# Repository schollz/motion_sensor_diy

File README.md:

motion_sensor_diy
=================

Electronic schematics for RF motion sensor that uses Arduino as receiver hub

Instructions
=================

The eagle schematics show the wiring for the Motion Sensor and the Receiver. Each is very simple, here is the run down:

<h1>Motion sensor + RF transmitter</h1>

<strong>Components</strong>
<ul>
<li><a href="https://www.google.com/url?sa=t&rct=j&q=&esrc=s&source=web&cd=6&cad=rja&uact=8&ved=0CDkQFjAF&url=http%3A%2F%2Fwww.mpja.com%2Fdownload%2F31227sc.pdf&ei=8FgzU868GsHLsQSTnYKIDg&usg=AFQjCNELdcZfKHaZhM4NlzFmhzu2_fOHwg&sig2=eFrgkllWo_47kU5vjeJpJA&bvm=bv.63738703,d.cWc">PIR sensor</a>, on <a href="http://www.amazon.com/HC-SR501-Sensor-Module-Pyroelectric-Infrared/dp/B007XQRKD4">Amazon</a> or <a href="http://www.ebay.com/itm/10pcs-HC-SR501-Adjust-IR-Pyroelectric-Infrared-PIR-Motion-Sensor-Detector-Module-/131028677440?pt=LH_DefaultDomain_0&hash=item1e81eaf340">Ebay</a></li>
<li><a href="http://www.100y.com.tw/pdf_file/PT2262-IRS.PDF">PT2262 encoder</a></li>
<li><a href="http://www.atmel.com/images/atmel-2586-avr-8-bit-microcontroller-attiny25-attiny45-attiny85_datasheet.pdf">ATtiny85</a></li>
<li><a href="http://www.amazon.com/433Mhz-transmitter-receiver-your-Experiment/dp/B00AMB3NCY">434 MHz RF transmitter</a></li>
<li>Several 500-1k Ohm resistors</li>
<li>LED (optional)</li>
</ul>

The motion sensor is simply a PIR sensor connected to a 434MHz RF transmitter via an encoder. The encoder uses four bits, in the form of resistors tied to HIGH (+VCC) or LOW (GND). That's enough for 12 sensors. 
The ATtiny85 is programmed via an Arduino which allows for devising a smart way of sending the RF data. It can be programmed to send the output as randomized timed sequences in order to reduce the conflicts of having other motion sensors on the same band.

<h1>RF Receiver</h1>

<strong>Components</strong>
<ul>
<li>Arduino</li>
<li>PT2272 encoder</li>
<li>434 MHz RF receiver</li>
</ul>

This circuit is even simpler. Connect the RF receiver output to the DIN of the PT2272. Then put each output pin (the four bits) into the Arduino pins 3-6. It's best to connect the VT (Viable Transmission indicator) pin of the PT2272 to the Pin 2 of the Arduino so that you can attach an interrupt on it. This way whenever VT goes high, the Arduino will read the other four pins and use that to determine which sensor is which (I leave this to you, though).

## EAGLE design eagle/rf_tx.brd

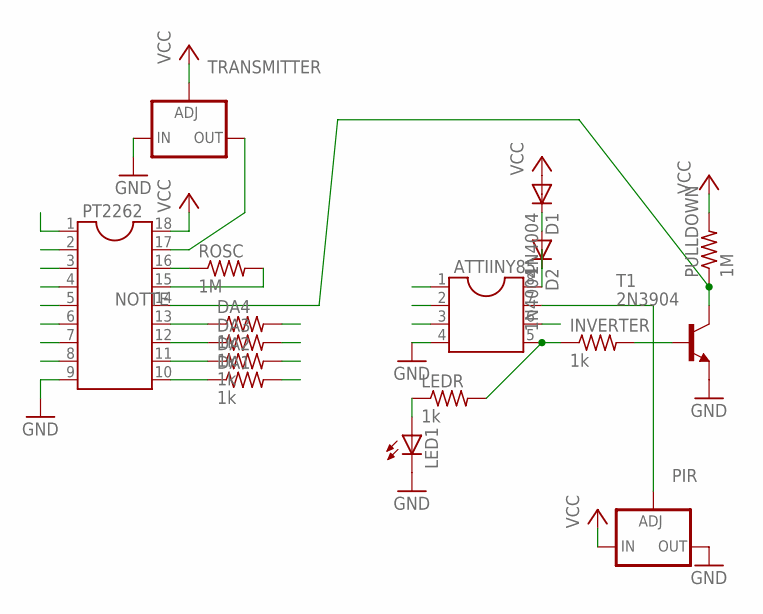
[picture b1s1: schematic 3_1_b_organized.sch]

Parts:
ATTIINY85: DIL8; DIL08
D1, D2: 1N4004; DO41-10
DA1, DA2, DA3, DA4: 1k; 0207/5V
INVERTER: 1k; 0207/5V
LED1: LED_ELD260; LED_LD260
LEDR: 1k; 0204/5
PIR: LM337TS; 337TS
PT2262: DIL18
PULLDOWN: 1M; 0207/5V
ROSC: 1M; 0204/5
T1: 2N3904; TO92
TRANSMITTER: LM337TS; 337TS

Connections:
GND: ATTIINY85.4, LED1.K (C), PIR.3 (OUT), PT2262.9, T1.3 (E), TRANSMITTER.2 (IN)
unnamed: D1.C, D2.A
unnamed: ATTIINY85.8, D2.C
unnamed: INVERTER.2, T1.2 (B)
unnamed: ATTIINY85.7, PIR.1 (ADJ)
unnamed: LED1.A, LEDR.1
unnamed: PT2262.17, TRANSMITTER.3 (OUT)
unnamed: PT2262.16, ROSC.1
unnamed: PT2262.15, ROSC.2
unnamed: DA1.1, PT2262.10
unnamed: DA3.1, PT2262.12
unnamed: DA2.1, PT2262.11
unnamed: DA4.1, PT2262.13
unnamed: ATTIINY85.5, INVERTER.1, LEDR.2
NOTTE: PT2262.14, PULLDOWN.1, T1.1 (C)
VCC: D1.A, PIR.2 (IN), PT2262.18, PULLDOWN.2, TRANSMITTER.1 (ADJ)

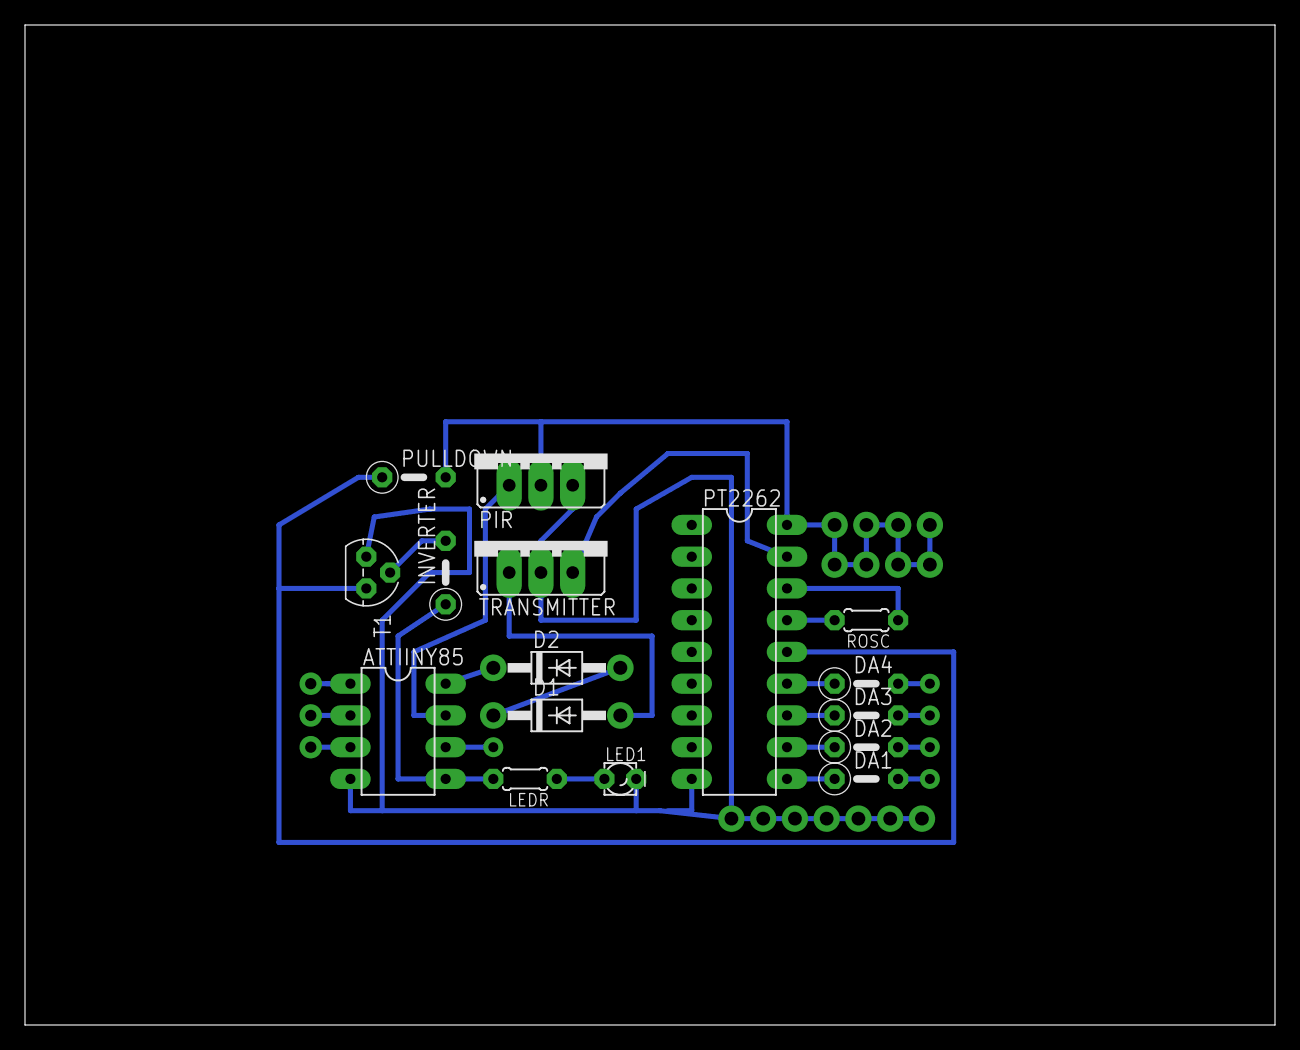
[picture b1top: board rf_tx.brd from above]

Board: 2 copper layers, 100.0 x 80.0 mm, 16 parts (0 on the bottom side), 16 nets.

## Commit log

2014-03-26 Create attiny_pir_rf_send
2014-03-26 added working boards
2014-03-26 Changed names
2014-03-26 Images and updated rx board
2014-03-26 arduino and attiny code updated
2014-03-26 Added in instructions
    will add urls for the components soon
